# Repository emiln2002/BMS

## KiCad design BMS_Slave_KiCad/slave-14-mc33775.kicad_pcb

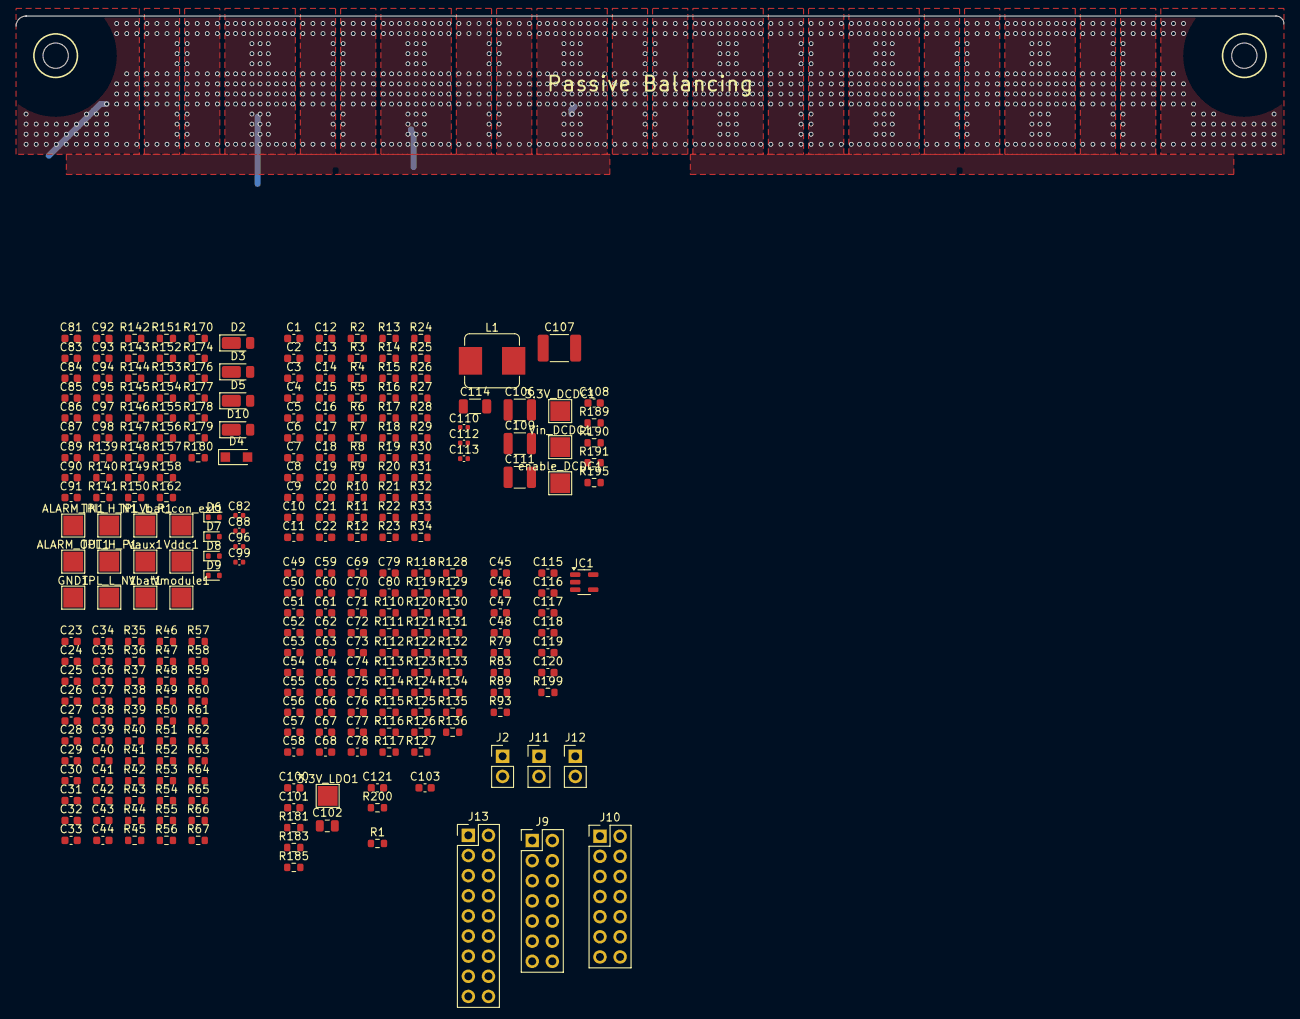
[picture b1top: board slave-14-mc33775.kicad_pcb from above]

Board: 6 copper layers, 289 parts (0 on the bottom side), 123 nets.

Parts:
3.3V_DCDC1, 3.3V_LDO1: Testpoint_Square; TestPoint_Pad_2.5x2.5mm
ALARM_IN1: Testpoint_Square; TestPoint_Pad_2.5x2.5mm
ALARM_OUT1: Testpoint_Square; TestPoint_Pad_2.5x2.5mm
C1, C2, C3, C4, C5, C6, C7, C8, C9, C10, C11, C12, C13, C14, C15, C16, C17, C18, C19, C20, C21, C22, C23, C24, C25, C26, C27, C28, C29, C30, C31, C32, C33, C34, C35, C36, C37, C38, C39, C40, C41, C42, C43, C44, C45, C46, C47, C48, C49, C50, C51, C52, C53, C54, C55, C56, C57, C58, C59, C60, C61, C62, C63, C64, C65, C66, C67, C68, C69, C70, C71, C72, C73, C74, C75, C76, C77, C78, C79, C80, C81, C83, C84, C85, C86, C87, C89, C90, C91, C92, C93, C94, C95, C97, C98, C100, C101, C103, C108, C115, C116, C117, C118, C119, C120, C121: 10 nF; C_0603_1608Metric
C82, C88, C96, C99, C110, C112, C113: 22pF; C_0402_1005Metric
C102: 2.2uF; C_0805_2012Metric
C106, C109, C111: 2.2uF; C_1210_3225Metric
C107: 3.3uF; C_1812_4532Metric
C114: 22u; C_1206_3216Metric
D2, D3, D10: Schottky_100V_1A; D_PowerDI-123
D4: PTVS60VS1UR; Nexperia_CFP3_SOD-123W
D5: S1MSP1-7; D_PowerDI-123
D6, D7, D8, D9: PESD5V0V1BB; D_SOD-523
GND1: Testpoint_Square; TestPoint_Pad_2.5x2.5mm
IC1: MCP9800A0T-M/OT; SOT-23-5
J2, J11, J12: Pinheader_2x1_vertical; PinHeader_1x02_P2.54mm_Vertical
J9, J10: Pinheader_2x7_vertical; PinHeader_2x07_P2.54mm_Vertical
J13: Pinheader_2x9_vertical; PinHeader_2x09_P2.54mm_Vertical
L1: 470nH; L_Bourns_SRP7028A_7.3x6.6mm
MP_UL: Hole_3.2_Iso
MP_UR: Hole_3.2_Iso
R1, R10, R11, R20, R21, R22, R23, R24, R25, R26, R27, R28, R29, R30, R32, R33, R34, R43, R44, R53, R54, R55, R56, R57, R58, R59, R60, R61, R62, R63, R65, R66, R67, R110, R111, R112, R113, R114, R115, R116, R117, R126, R127, R128, R139, R140, R141, R142, R143, R144, R145, R146, R147, R148, R149, R150, R151, R152, R153, R154, R155, R156, R157, R158, R162, R170, R174, R176, R177, R178, R179, R180, R181, R183, R185, R189, R191, R195: 0; R_0603_1608Metric
R2, R3, R4, R5, R6, R7, R8, R9, R35, R36, R37, R38, R39, R40, R41, R42, R79, R83, R89, R93, R118, R119, R120, R121, R122, R123, R124, R125, R129, R130, R131, R132, R133, R134, R135, R136, R190, R199, R200: 10K; R_0603_1608Metric
R12, R13, R14, R15, R16, R17, R18, R19, R31, R45, R46, R47, R48, R49, R50, R51, R52, R64: 1K; R_0603_1608Metric
TPL_H_N1: Testpoint_Square; TestPoint_Pad_2.5x2.5mm
TPL_H_P1: Testpoint_Square; TestPoint_Pad_2.5x2.5mm
TPL_L_N1: Testpoint_Square; TestPoint_Pad_2.5x2.5mm
TPL_L_P1: Testpoint_Square; TestPoint_Pad_2.5x2.5mm
Vaux1: Testpoint_Square; TestPoint_Pad_2.5x2.5mm
Vbat1: Testpoint_Square; TestPoint_Pad_2.5x2.5mm
Vbat_con_ext1: Testpoint_Square; TestPoint_Pad_2.5x2.5mm
Vddc1: Testpoint_Square; TestPoint_Pad_2.5x2.5mm
Vin_DCDC1: Testpoint_Square; TestPoint_Pad_2.5x2.5mm
Vmodule1: Testpoint_Square; TestPoint_Pad_2.5x2.5mm
enable_DCDC1: Testpoint_Square; TestPoint_Pad_2.5x2.5mm

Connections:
+3.3V: 3.3V_DCDC1.1, C113.2, C114.2, C120.2, J9.10, J10.10, R195.2
/U_analog_in_bank0/A0: R29.1, R30.2
/U_analog_in_bank0/A1: R33.1, R34.2
/U_analog_in_bank0/D: R27.1, R32.1
/U_analog_in_bank0/D_amp: R27.2, R31.1
/U_analog_in_bank0/MUX-DATA_IN: R1.1, R32.2
/U_analog_in_bank0/S1: C12.2, R12.1, R20.1
/U_analog_in_bank0/S2: C13.2, R13.1, R21.1
/U_analog_in_bank0/S3: C14.2, R14.1, R22.1
/U_analog_in_bank0/S4: C15.2, R15.1, R23.1
/U_analog_in_bank0/S5: C16.2, R16.1, R24.1
/U_analog_in_bank0/S6: C17.2, R17.1, R25.1
/U_analog_in_bank0/S7: C18.2, R18.1, R26.1
/U_analog_in_bank0/S8: C19.2, R19.1, R28.1
/U_analog_in_bank0/T-SENSOR_0: C1.2, R9.1, R12.2
/U_analog_in_bank0/T-SENSOR_1: C3.2, R8.1, R13.2
/U_analog_in_bank0/T-SENSOR_2: C4.2, R7.1, R14.2
/U_analog_in_bank0/T-SENSOR_3: C5.2, R6.1, R15.2
/U_analog_in_bank0/T-SENSOR_4: C6.2, R5.1, R16.2
/U_analog_in_bank0/T-SENSOR_5: C8.2, R4.1, R17.2
/U_analog_in_bank0/T-SENSOR_6: C10.2, R3.1, R18.2
/U_analog_in_bank0/T-SENSOR_7: C11.2, R2.1, R19.2
/U_analog_in_bank0/T_FILT0: R20.2, R155.1
/U_analog_in_bank0/T_FILT1: R21.2, R141.1
/U_analog_in_bank0/T_FILT2: R22.2, R156.1
/U_analog_in_bank0/T_FILT3: R23.2, R142.1
/U_analog_in_bank0/T_FILT4: R24.2, R157.1
/U_analog_in_bank0/T_FILT5: R25.2, R143.1
/U_analog_in_bank0/T_FILT6: R26.2, R158.1
/U_analog_in_bank0/T_FILT7: R28.2, R144.1
/U_analog_in_bank1/A0: R62.1, R63.2
/U_analog_in_bank1/A1: R66.1, R67.2
/U_analog_in_bank1/D: R60.1, R65.1
/U_analog_in_bank1/D_amp: R60.2, R64.1
/U_analog_in_bank1/S1: C34.2, R45.1, R53.1
/U_analog_in_bank1/S2: C35.2, R46.1, R54.1
/U_analog_in_bank1/S3: C36.2, R47.1, R55.1
/U_analog_in_bank1/S4: C37.2, R48.1, R56.1
/U_analog_in_bank1/S5: C38.2, R49.1, R57.1
/U_analog_in_bank1/S6: C39.2, R50.1, R58.1
/U_analog_in_bank1/S7: C40.2, R51.1, R59.1
/U_analog_in_bank1/S8: C41.2, R52.1, R61.1
/U_analog_in_bank1/T-SENSOR_0: C23.2, R42.1, R45.2
/U_analog_in_bank1/T-SENSOR_1: C25.2, R41.1, R46.2
/U_analog_in_bank1/T-SENSOR_2: C26.2, R40.1, R47.2
/U_analog_in_bank1/T-SENSOR_3: C27.2, R39.1, R48.2
/U_analog_in_bank1/T-SENSOR_4: C28.2, R38.1, R49.2
/U_analog_in_bank1/T-SENSOR_5: C30.2, R37.1, R50.2
/U_analog_in_bank1/T-SENSOR_6: C32.2, R36.1, R51.2
/U_analog_in_bank1/T-SENSOR_7: C33.2, R35.1, R52.2
/U_connectors/ALARM_IN: ALARM_IN1.1, J9.7, J10.7, R146.1
/U_connectors/ALARM_OUT: ALARM_OUT1.1, J9.8, J10.8
/U_connectors/CIN0: C73.2, R136.2
/U_connectors/CIN1: C72.2, R135.2
/U_connectors/CIN2: C71.2, R134.2
/U_connectors/CIN3: C70.2, R133.2
/U_connectors/CIN4: C69.2, R110.1, R132.2
/U_connectors/CIN5: C68.2, R111.1, R131.2
/U_connectors/CIN6: C67.2, R112.1, R130.2
/U_connectors/CIN7: C56.2, R113.1, R125.2
/U_connectors/CIN8: C55.2, R114.1, R124.2
/U_connectors/CIN9: C54.2, R115.1, R123.2
/U_connectors/CIN10: C53.2, R116.1, R122.2
/U_connectors/CIN11: C52.2, R117.1, R121.2
/U_connectors/CIN12: C51.2, R120.2, R126.1
/U_connectors/CIN13: C50.2, R119.2, R127.1
/U_connectors/CIN14: C49.2, R118.2, R128.1
/U_connectors/DIGITAL-IO_2: IC1.3 (ALERT), J13.3, R199.1
/U_connectors/GPIO2_ext: J9.1, J10.1
/U_connectors/GPIO3_ext: J9.2, J10.2
/U_connectors/GPIO6_ext: J9.3, J10.3
/U_connectors/GPIO7_ext: J9.4, J10.4
/U_connectors/SCL: J9.5, J10.5
/U_connectors/SDA: J9.6, J10.6
/U_dcdc-converter/EnableDC/DC: R176.2, R189.1
/U_dcdc-converter/Enable_DCDC: R189.2, R190.1, enable_DCDC1.1
/U_dcdc-converter/VBAT_con_ext_emi: C106.2, C108.2, C109.2, C111.2, L1.2, R191.2, Vin_DCDC1.1
/U_dcdc-converter/VBAT_con_ext_lim: L1.1, R191.1
/U_input_filter/CT0: C80.2, R136.1
/U_input_filter/CT1: C79.2, R135.1
/U_input_filter/CT2: C78.2, R134.1
/U_input_filter/CT3: C77.2, R133.1
/U_input_filter/CT4: C76.2, R132.1
/U_input_filter/CT5: C75.2, R131.1
/U_input_filter/CT6: C74.2, R130.1
/U_input_filter/CT7: C64.2, R125.1
/U_input_filter/CT8: C63.2, R124.1
/U_input_filter/CT9: C62.2, R123.1
/U_input_filter/CT10: C61.2, R122.1
/U_input_filter/CT11: C60.2, R121.1
/U_input_filter/CT12: C59.2, R120.1
/U_input_filter/CT13: C58.2, R119.1
/U_input_filter/CT14: C57.2, R118.1
/U_input_filter/Vmodule_unfiltered: C65.2, R110.2, R111.2, R112.2, R113.2, R114.2, R115.2, R116.2, R117.2, R126.2, R127.2, R128.2, R129.2
/U_mc33775/BAL_NTC0: C46.2, R83.1, R149.1
/U_mc33775/BAL_NTC1: C48.2, R93.1, R150.1
/U_mc33775/GPIO0: R145.2, R155.2
/U_mc33775/GPIO1: R141.2, R146.2
/U_mc33775/GPIO2: R147.2, R153.2, R156.2
/U_mc33775/GPIO3: R139.2, R142.2, R149.2
/U_mc33775/GPIO4: R151.2, R157.2
/U_mc33775/GPIO5: R143.2, R152.2
/U_mc33775/GPIO6: R148.2, R154.2, R158.2
/U_mc33775/GPIO7: R140.2, R144.2, R150.2
/U_mc33775/MUX_DATA: C22.2, R31.2, R145.1
/U_mc33775/MUX_DATA2: C44.2, R1.2, R64.2, R147.1
/U_mc33775/RXTXH_N: C93.1, D7.1 (C), TPL_H_N1.1
/U_mc33775/RXTXH_P: C92.2, D6.1 (C), TPL_H_P1.1
/U_mc33775/RXTXL_N: C95.1, D9.1 (C), TPL_L_N1.1
/U_mc33775/RXTXL_P: C94.2, D8.1 (C), TPL_L_P1.1
GND: C1.1, C2.1, C3.1, C4.1, C5.1, C6.1, C7.1, C8.1, C9.1, C10.1, C11.1, C12.1, C13.1, C14.1, C15.1, C16.1, C17.1, C18.1, C19.1, C20.1, C21.1, C22.1, C23.1, C24.1, C25.1, C26.1, C27.1, C28.1, C29.1, C30.1, C31.1, C32.1, C33.1, C34.1, C35.1, C36.1, C37.1, C38.1, C39.1, C40.1, C41.1, C42.1, C43.1, C44.1, C45.1, C46.1, C47.1, C48.1, C49.1, C50.1, C51.1, C52.1, C53.1, C54.1, C55.1, C56.1, C57.1, C58.1, C59.1, C60.1, C61.1, C62.1, C63.1, C64.1, C65.1, C66.1, C67.1, C68.1, C69.1, C70.1, C71.1, C72.1, C73.1, C74.1, C75.1, C76.1, C77.1, C78.1, C79.1, C80.1, C81.1, C83.1, C84.1, C85.1, C86.1, C87.1, C88.1, C89.1, C90.1, C91.1, C92.1, C93.2, C94.1, C95.2, C96.1, C97.1, C98.1, C100.1, C101.1, C102.1, C103.1, C106.1, C107.1, C108.1, C109.1, C111.1, C114.1, C115.1, C116.1, C117.1, C118.1, C119.1, C120.1, C121.1, D4.2 (A), D6.2 (A), D7.2 (A), D8.2 (A), D9.2 (A), GND1.1, IC1.2 (GND), J2.2, J9.13, J9.14, J10.13, J10.14, J11.2, J12.2, J13.17, J13.18, R30.1, R34.1, R63.1, R67.1, R190.2
unnamed: C2.2, R2.2, R3.2, R4.2, R5.2, R6.2, R7.2, R8.2, R9.2, R10.1, R11.1
unnamed: C24.2, R35.2, R36.2, R37.2, R38.2, R39.2, R40.2, R41.2, R42.2, R43.1, R44.1
unnamed: C45.2, R79.1, R83.2
unnamed: C47.2, R89.1, R93.2
unnamed: C112.2, C113.1
VAUX: C85.2, C87.2, C89.2, C91.2, J9.12, J10.12, R10.2, R43.2, R79.2, R89.2, R174.2, Vaux1.1
VBAT: C83.2, Vbat1.1
VBAT_con_ext: C81.2, D2.1 (K), D3.1 (K), D4.1 (C), D5.1 (K), J11.1, J12.1, Vbat_con_ext1.1
VBAT_ext: D3.2 (A), J2.1
VDDC: C7.2, C9.2, C29.2, C31.2, C84.2, C86.2, C100.2, D10.2 (A), J9.11, J10.11, R162.2, R170.2, R176.1, R181.2, Vddc1.1
VDDIO: 3.3V_LDO1.1, C20.2, C21.2, C42.2, C43.2, C102.2, C103.2, C115.2, C116.2, C117.2, C118.2, C119.2, C121.2, IC1.1 (VDD), J9.9, J10.9, R29.2, R33.2, R62.2, R66.2, R162.1, R183.2, R185.1, R185.2, R199.2, R200.1
VMODULE: C66.2, R129.1, Vmodule1.1

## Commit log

2025-12-06 fixt smalle problem i slave, i will need a hand to look at it further
2025-12-10 design ruel chekker is up to date
2025-12-10 addet output files
2026-01-15 Commit update
2026-02-12 nu i KiCad
2026-02-12 noget af diagram tegningen er opdateret, vi fortsætter
2026-02-12 Updated footprints - halfway done
2026-02-16 jeg har tilføjet 18 celles bms slave, men jeg har problemer med altium og kan derfor ikke redigere det... Der er 6 2-pins stik, 2 16-pins og 1 24-pins stik der skal laves om til wurt stik. Det bør ku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
2026-02-16 chip datasheet
2026-03-07 Skiftet connektors på slave
2026-03-08 Jeg har conetet de nederste stik hvor de skal være, så skal der laves plads til de 3 sidste (X400, X401, X900). Jeg er i gang med X400 og X401.
2026-03-18 De sidste stik er routed, der mangler stadig noget oprydning og så skal der findes en god måde at måle den præcise lokation på.
2026-04-08 all relevent problems from drc is fixed, shoud be redy for rewiv
2026-05-06 Depopulation of components
